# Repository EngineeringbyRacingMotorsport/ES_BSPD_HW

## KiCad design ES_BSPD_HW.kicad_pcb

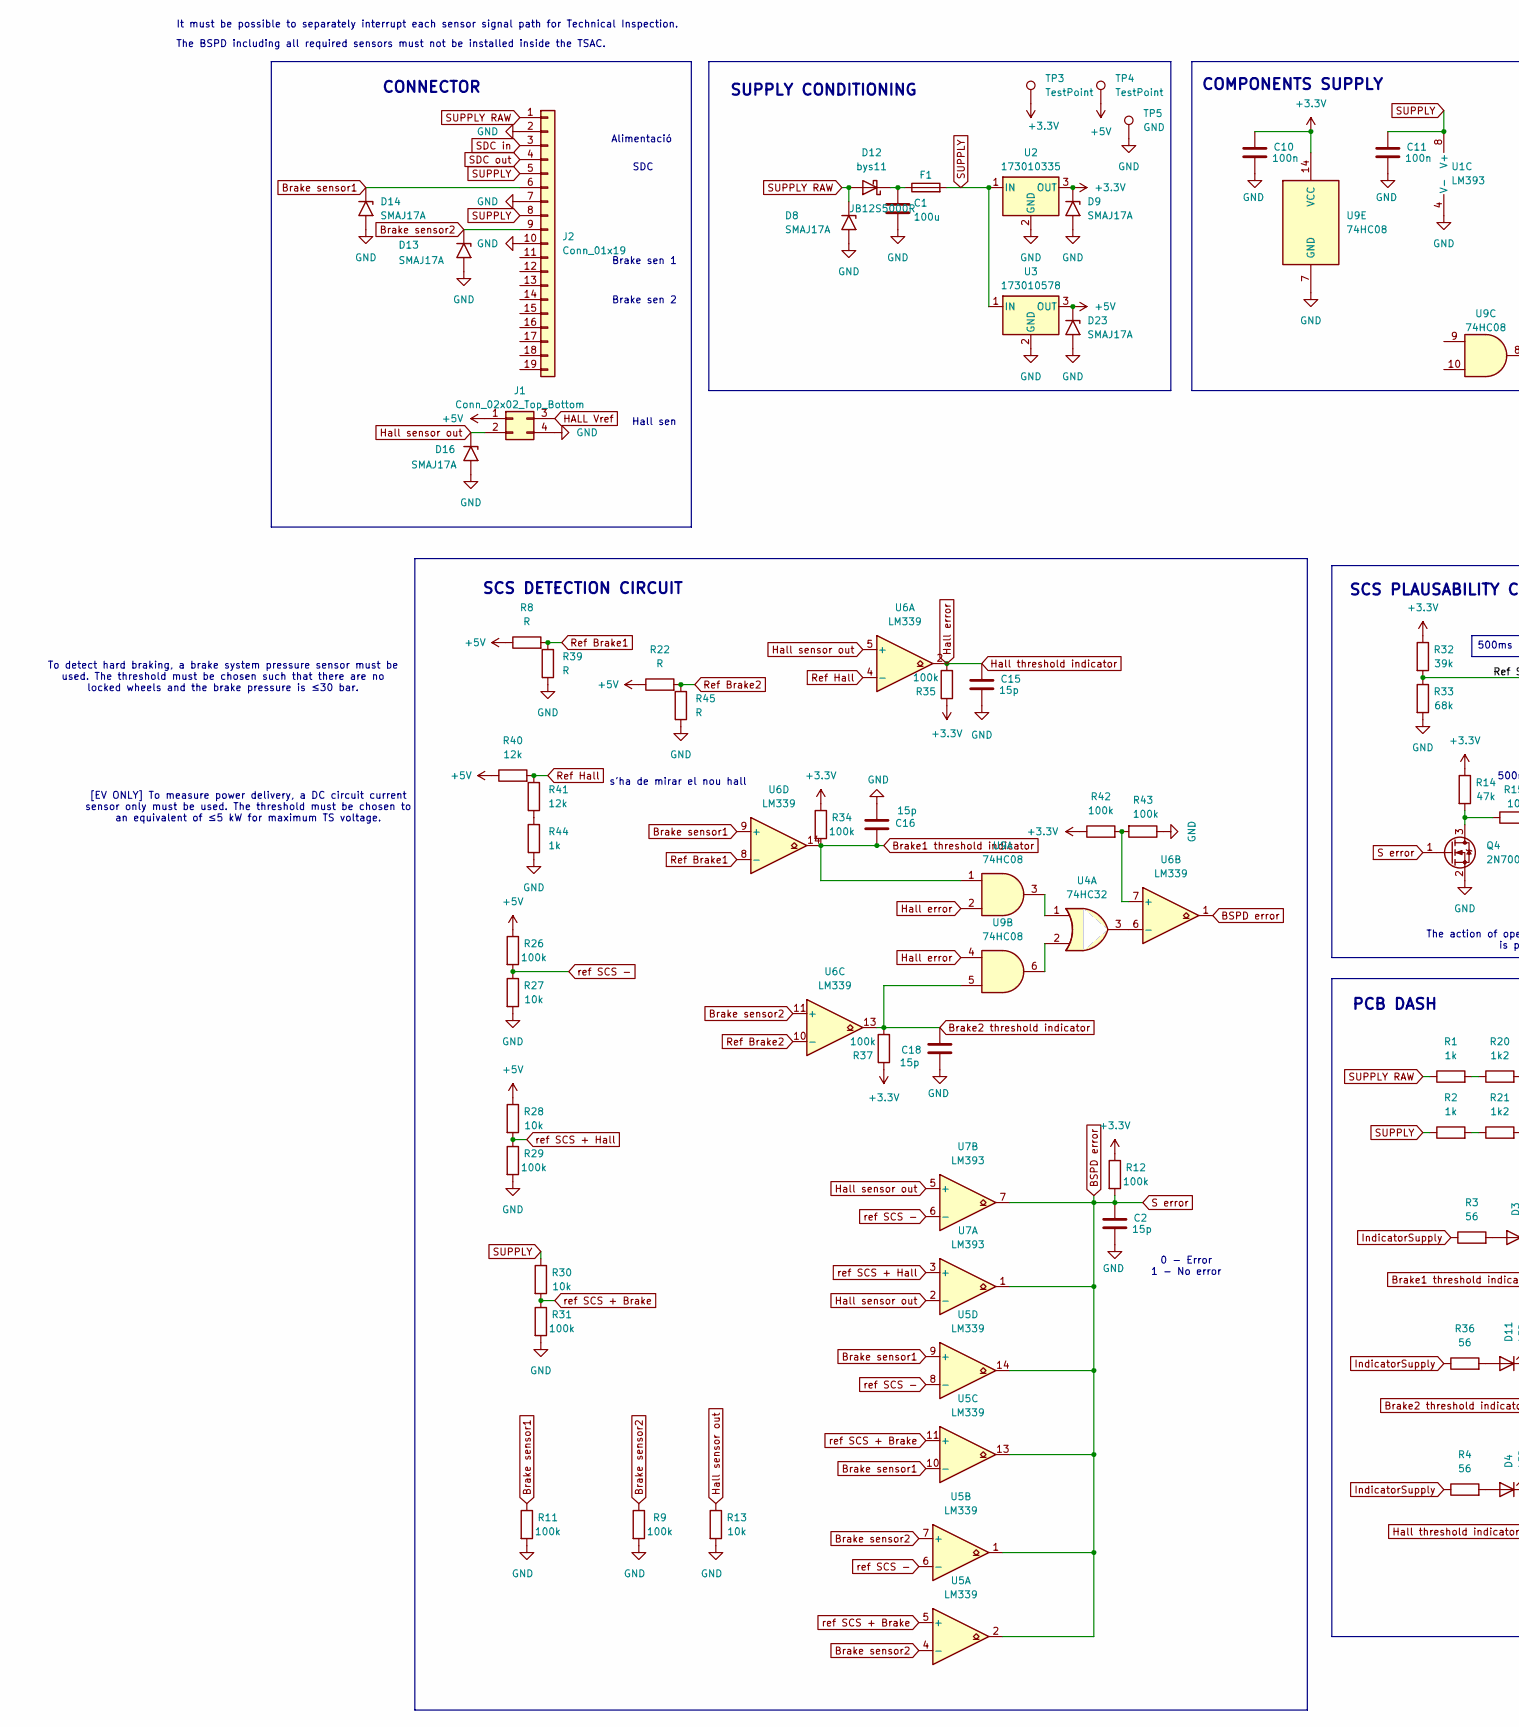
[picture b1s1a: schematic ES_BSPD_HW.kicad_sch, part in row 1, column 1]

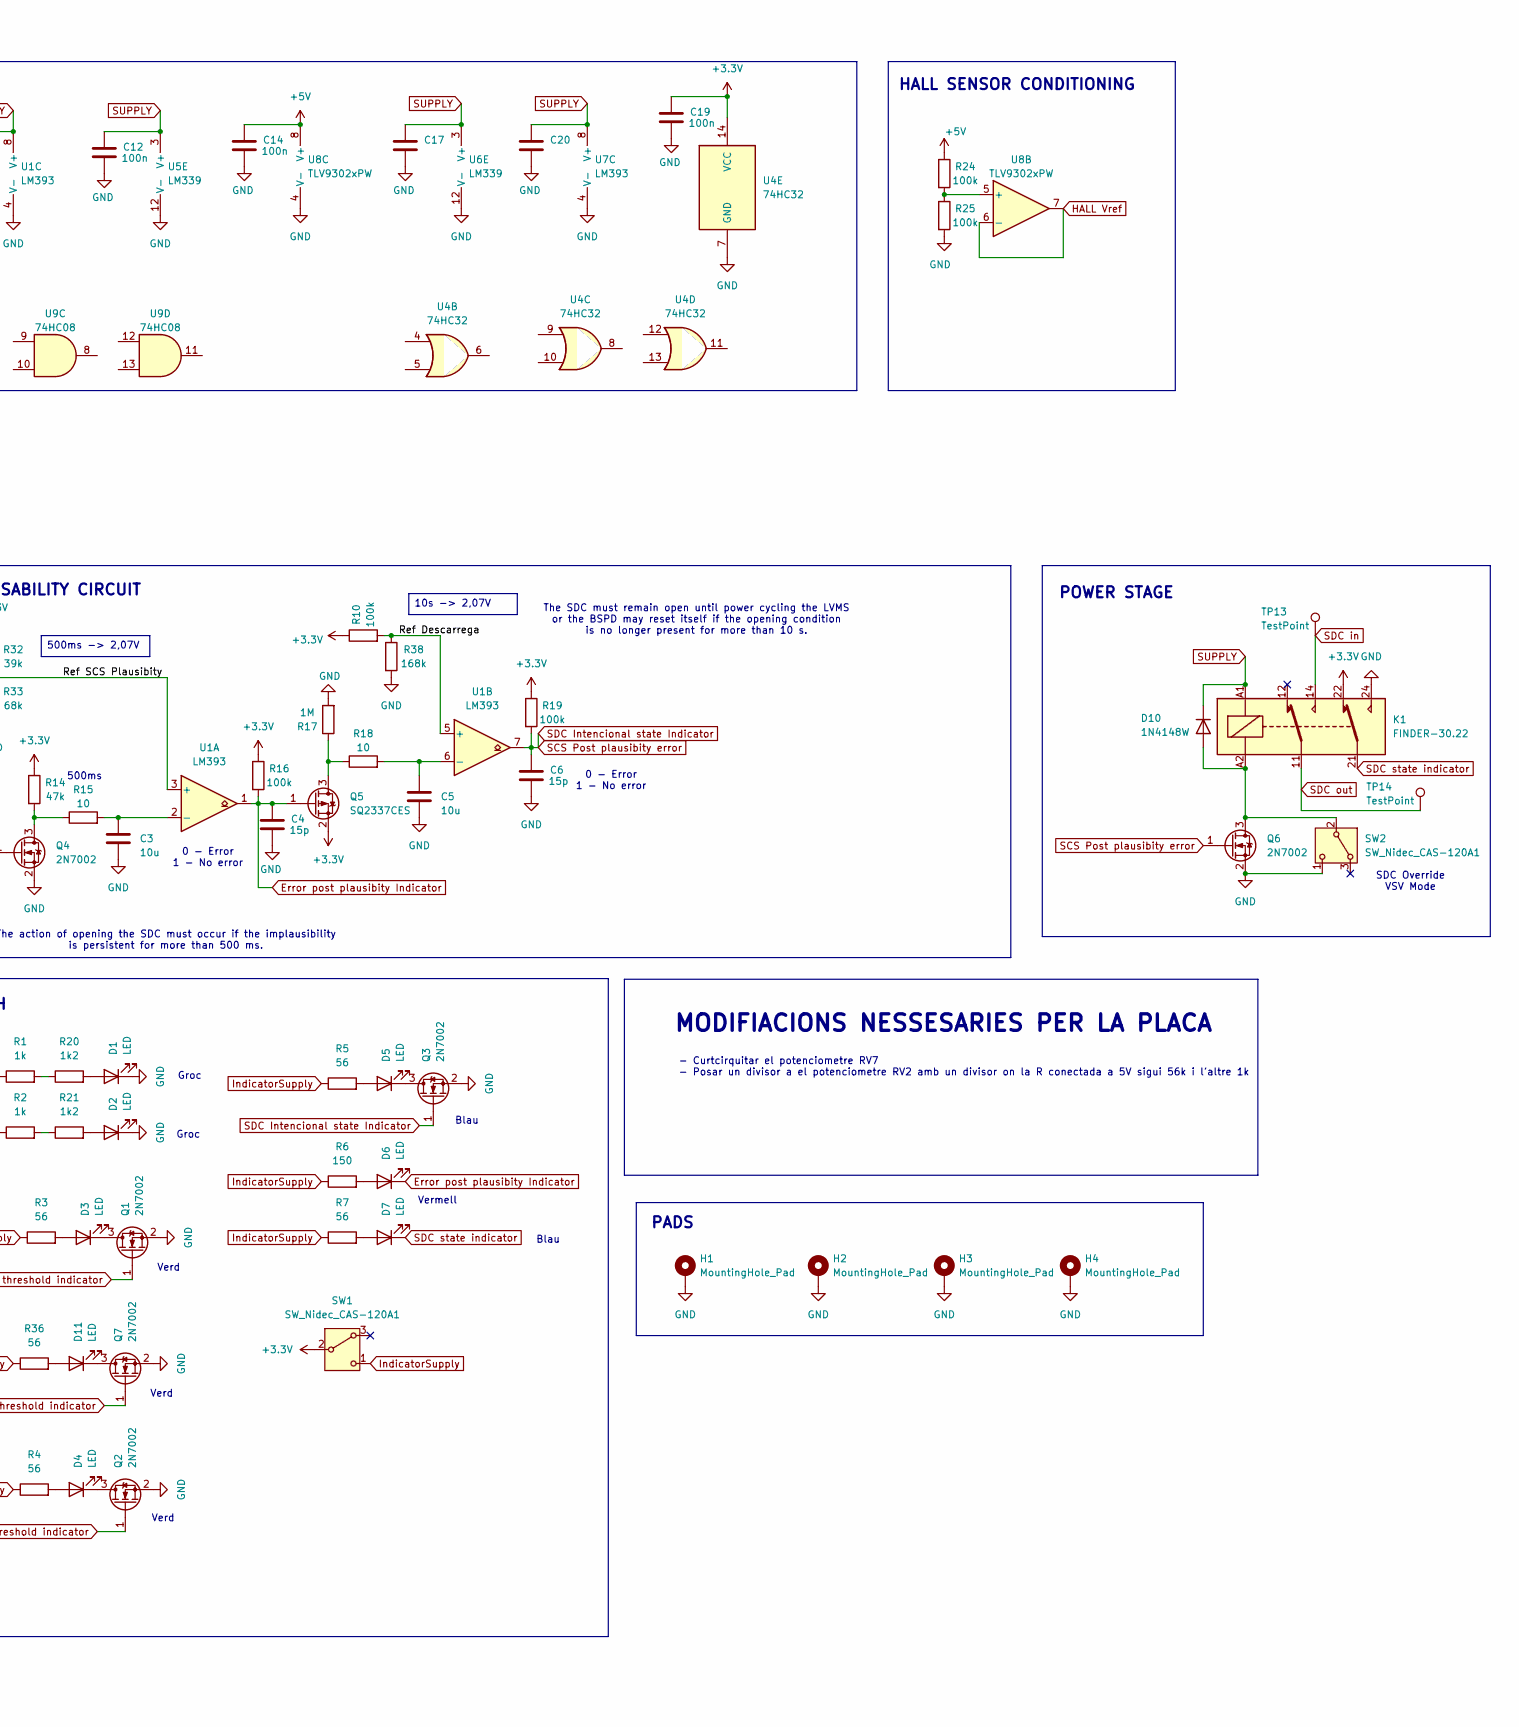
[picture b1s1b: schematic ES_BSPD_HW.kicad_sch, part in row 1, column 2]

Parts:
C1: 100u; CP_Elec_10x10
C2, C4, C6, C15, C16, C18: 15p; C_0603_1608Metric
C3, C5: 10u; C_0603_1608Metric
C10, C11, C12, C14, C17, C19, C20: 100n; C_0603_1608Metric
D1, D2, D3, D4, D5, D6, D7, D11: LED; LED_0603_1608Metric
D8, D9, D13, D14, D16, D23: SMAJ17A; D_SMB
D10: 1N4148W; D_SOD-123
D12: bys11; D_SMA
F1: JB12S5000R; Fuse_1206_3216Metric
H1, H2, H3, H4: MountingHole_Pad; MountingHole_3.5mm_Pad_Via
J1: Conn_02x02_Top_Bottom; Molex_Nano-Fit_105310-xx04_2x02_P2.50mm_Vertical
J2: Conn_01x19; CKB.M19.GLVG
K1: FINDER-30.22; Relay_DPDT_Finder_30.22
Q1, Q2, Q3, Q4, Q6, Q7: 2N7002; SOT-23
Q5: SQ2337CES; SOT-23
R1, R2: 1k; R_1206_3216Metric
R3, R4, R5, R7, R36: 56; R_0603_1608Metric
R6: 150; R_0603_1608Metric
R8, R22, R39, R45: R; R_0603_1608Metric
R9, R10, R11, R12, R16, R19, R24, R25, R26, R29, R31, R34, R35, R37, R42, R43: 100k; R_0603_1608Metric
R13, R27, R28, R30: 10k; R_0603_1608Metric
R14: 47k; R_0603_1608Metric
R15, R18: 10; R_0603_1608Metric
R17: 1M; R_0603_1608Metric
R20, R21: 1k2; R_1206_3216Metric
R32: 39k; R_0603_1608Metric
R33: 68k; R_0603_1608Metric
R38: 168k; R_0603_1608Metric
R40, R41: 12k; R_0603_1608Metric
R44: 1k; R_0603_1608Metric
SW1, SW2: SW_Nidec_CAS-120A1; Nidec_Copal_CAS-120A
TP3, TP4, TP13, TP14: TestPoint; TestPoint_Pad_D1.0mm
TP5: GND; TestPoint_Pad_D1.0mm
U1, U7: LM393; TSSOP-8_4.4x3mm_P0.65mm
U2: 173010335; Converter_DCDC_RECOM_R-78E-0.5_THT
U3: 173010578; Converter_DCDC_RECOM_R-78E-0.5_THT
U4: 74HC32; TSSOP-14_4.4x5mm_P0.65mm
U5, U6: LM339; TSSOP-14_4.4x5mm_P0.65mm
U8: TLV9302xPW; TSSOP-8_4.4x3mm_P0.65mm
U9: 74HC08; TSSOP-14_4.4x5mm_P0.65mm

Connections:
+3.3V: C10.1, C19.1, D9.1 (A1), K1.22, Q5.2 (S), R10.1, R12.1, R14.1, R16.1, R19.1, R32.1, R34.1, R35.1, R37.1, R42.1, SW1.2 (B), TP3.1, U2.3 (OUT), U4.14 (VCC), U9.14 (VCC)
+5V: C14.1, D23.1 (A1), J1.1, R8.1, R22.1, R24.1, R26.1, R28.1, R40.1, TP4.1, U3.3 (OUT), U8.8 (V+)
/Ref Descarrega: R10.2, R38.1, U1.5 (+)
/Ref SCS Plausibity: R32.2, R33.1, U1.3 (+)
BSPD error: C2.1, Q4.1 (G), R12.2, U5.1, U5.2, U5.13, U5.14, U6.1, U7.1, U7.7
Brake1 threshold indicator: C16.1, Q1.1 (G), R34.2, U6.14, U9.1
Brake2 threshold indicator: C18.1, Q7.1 (G), R37.2, U6.13, U9.5
Brake sensor1: D14.1 (A1), J2.6, R11.1, U5.9 (+), U5.10 (-), U6.9 (+)
Brake sensor2: D13.1 (A1), J2.9, R9.1, U5.4 (-), U5.7 (+), U6.11 (+)
Error post plausibity Indicator: C4.1, D6.1 (K), Q5.1 (G), R16.2, U1.1
GND: C1.2, C2.2, C3.2, C4.2, C5.2, C6.2, C10.2, C11.2, C12.2, C14.2, C15.2, C16.2, C17.2, C18.2, C19.2, C20.2, D1.1 (K), D2.1 (K), D8.2 (A2), D9.2 (A2), D13.2 (A2), D14.2 (A2), D16.2 (A2), D23.2 (A2), H1.1 (1_1), H2.1 (1_1), H3.1 (1_1), H4.1 (1_1), J1.4, J2.2, J2.7, J2.10, K1.24, Q1.2 (S), Q2.2 (S), Q3.2 (S), Q4.2 (S), Q6.2 (S), Q7.2 (S), R9.2, R11.2, R13.2, R17.2, R25.2, R27.2, R29.2, R31.2, R33.2, R38.2, R39.1, R43.1, R44.1, R45.1, SW2.1 (C), TP5.1, U1.4 (V-), U2.2 (GND), U3.2 (GND), U4.7 (GND), U5.12 (V-), U6.12 (V-), U7.4 (V-), U8.4 (V-), U9.7 (GND)
HALL Vref: J1.3, U8.6 (-), U8.7
Hall error: C15.1, Q2.1 (G), R35.2, U6.2, U9.2, U9.4
Hall sensor out: D16.1 (A1), J1.2, R13.1, U6.5 (+), U7.2 (-), U7.5 (+)
IndicatorSupply: R3.1, R4.1, R5.1, R6.1, R7.1, R36.1, SW1.1 (C)
unnamed: D1.2 (A), R20.2
unnamed: D2.2 (A), R21.2
unnamed: D3.2 (A), R3.2
unnamed: D3.1 (K), Q1.3 (D)
unnamed: D4.2 (A), R4.2
unnamed: D4.1 (K), Q2.3 (D)
unnamed: D5.2 (A), R5.2
unnamed: D5.1 (K), Q3.3 (D)
unnamed: D6.2 (A), R6.2
unnamed: D7.2 (A), R7.2
unnamed: D10.2 (A), K1.A2, Q6.3 (D), SW2.2 (B)
unnamed: D11.2 (A), R36.2
unnamed: D11.1 (K), Q7.3 (D)
unnamed: C1.1, D12.1 (K), F1.1
unnamed: Q4.3 (D), R14.2, R15.1
unnamed: Q5.3 (D), R17.1, R18.1
unnamed: R1.2, R20.1
unnamed: R2.2, R21.1
unnamed: R41.1, R44.2
unnamed: C3.1, R15.2, U1.2 (-)
unnamed: C5.1, R18.2, U1.6 (-)
unnamed: U4.1, U9.3
unnamed: U4.2, U9.6
unnamed: R42.2, R43.2, U6.7 (+)
unnamed: U4.3, U6.6 (-)
unnamed: R24.2, R25.1, U8.5 (+)
Ref Brake1: R8.2, R39.2, U6.8 (-)
Ref Brake2: R22.2, R45.2, U6.10 (-)
Ref Hall: R40.2, R41.2, U6.4 (-)
SCS Post plausibity error: C6.1, Q3.1 (G), Q6.1 (G), R19.2, U1.7
SDC in: J2.3, K1.14, TP13.1
SDC out: J2.4, K1.11, TP14.1
SDC state indicator: D7.1 (K), K1.21
SUPPLY: C11.1, C12.1, C17.1, C20.1, D10.1 (K), F1.2, J2.5, J2.8, K1.A1, R2.1, R30.1, U1.8 (V+), U2.1 (IN), U3.1 (IN), U5.3 (V+), U6.3 (V+), U7.8 (V+)
SUPPLY RAW: D8.1 (A1), D12.2 (A), J2.1, R1.1
ref SCS + Brake: R30.2, R31.1, U5.5 (+), U5.11 (+)
ref SCS + Hall: R28.2, R29.1, U7.3 (+)
ref SCS -: R26.2, R27.1, U5.6 (-), U5.8 (-), U7.6 (-)

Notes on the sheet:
SCS PLAUSABILITY CIRCUIT
SDC
Groc
[EV ONLY] To measure power delivery, a DC circuit current sensor only must be used. The threshold must be chosen to an equivalent of ≤5 kW for maximum TS voltage.
0 - Error 1 - No error
HALL SENSOR CONDITIONING
Blau
PADS
The action of opening the SDC must occur if the implausibility is persistent for more than 500 ms.
PCB DASH
Brake sen 1
The SDC must remain open until power cycling the LVMS or the BSPD may reset itself if the opening condition is no longer present for more than 10 s.
- Curtcirquitar el potenciometre RV7 - Posar un divisor a el potenciometre RV2 amb un divisor on la R conectada a 5V sigui 56k i l'altre 1k
s'ha de mirar el nou hall
Brake sen 2
COMPONENTS SUPPLY
Verd
Alimentació
Hall sen
SUPPLY CONDITIONING
It must be possible to separately interrupt each sensor signal path for Technical Inspection.
SCS DETECTION CIRCUIT
POWER STAGE
500ms
MODIFIACIONS NESSESARIES PER LA PLACA
To detect hard braking, a brake system pressure sensor must be used. The threshold must be chosen such that there are no locked wheels and the brake pressure is ≤30 bar.
Vermell
SDC Override VSV Mode
The BSPD including all required sensors must not be installed inside the TSAC.
CONNECTOR
500ms -> 2,07V
10s -> 2,07V

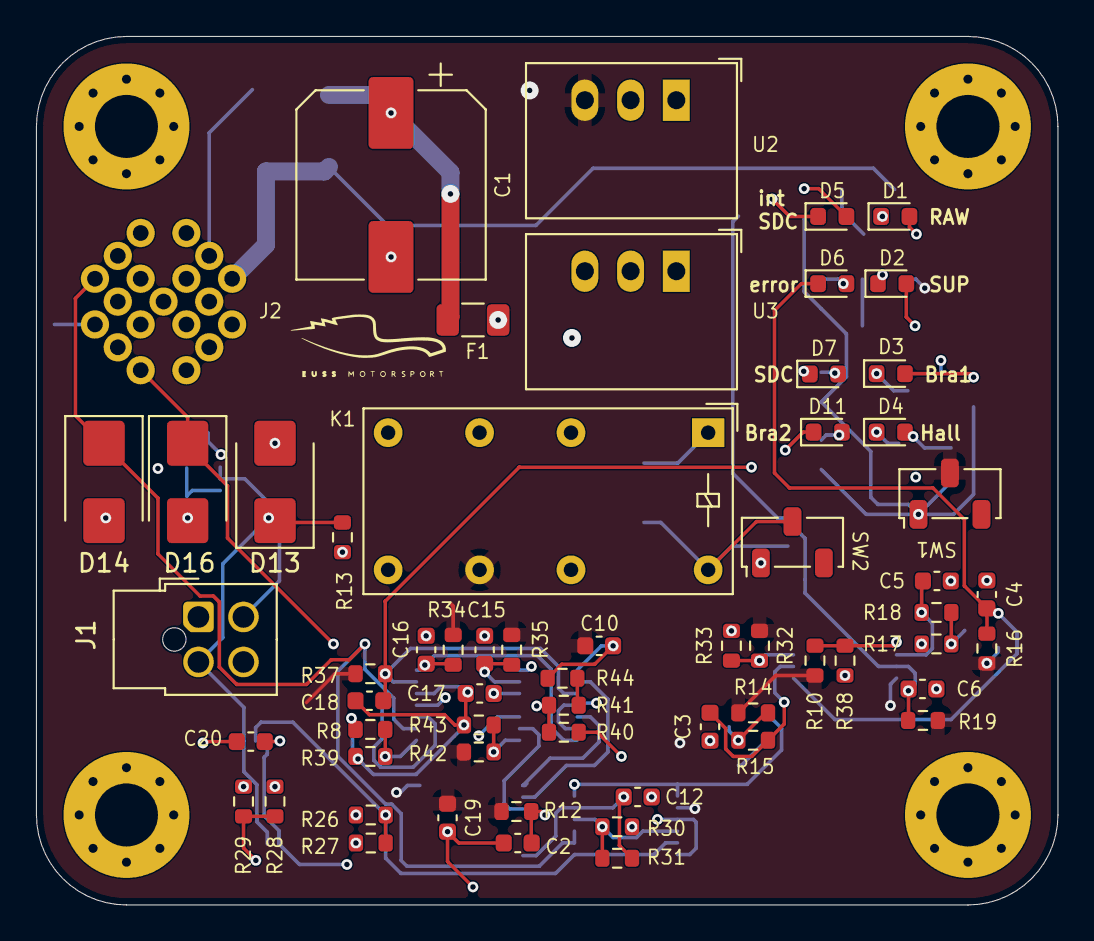
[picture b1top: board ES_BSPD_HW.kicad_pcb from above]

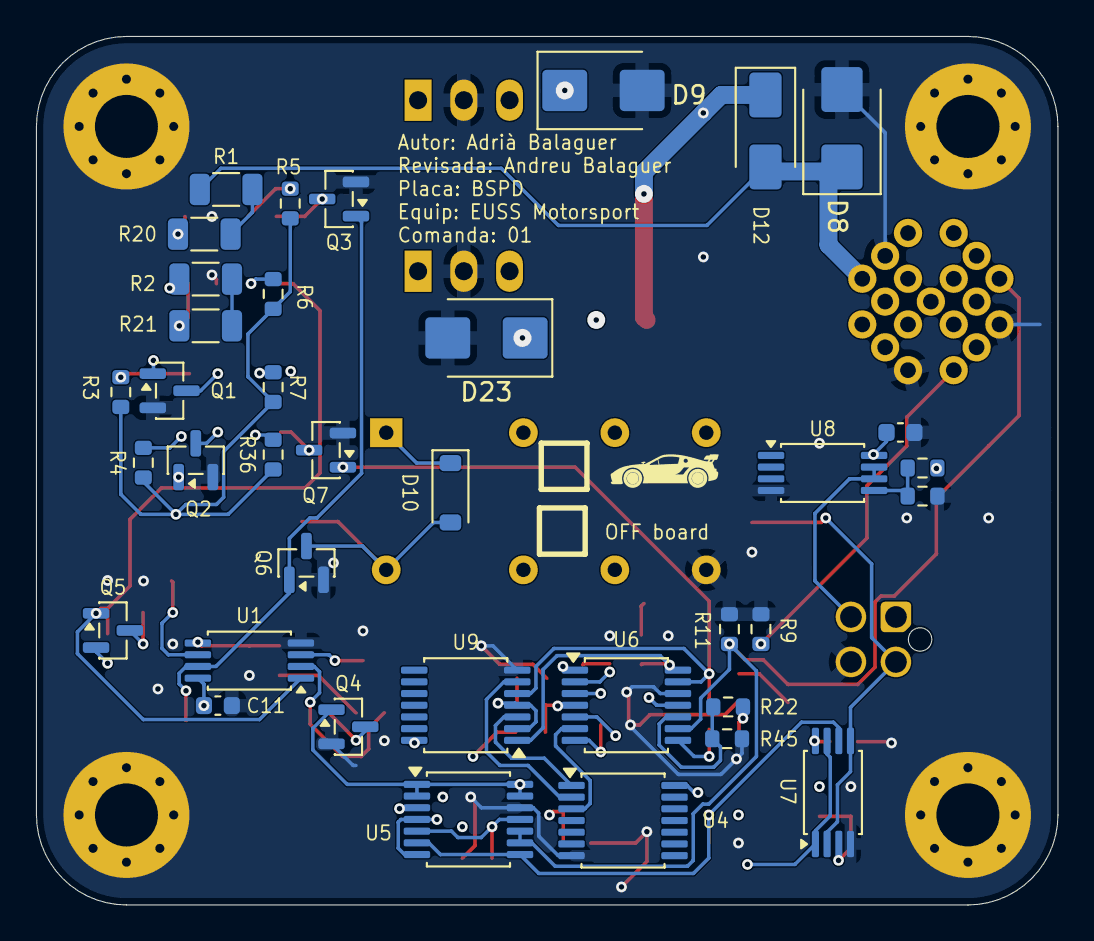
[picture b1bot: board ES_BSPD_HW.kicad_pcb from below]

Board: 4 copper layers, 56.8 x 48.2 mm, 102 parts (37 on the bottom side), 53 nets.

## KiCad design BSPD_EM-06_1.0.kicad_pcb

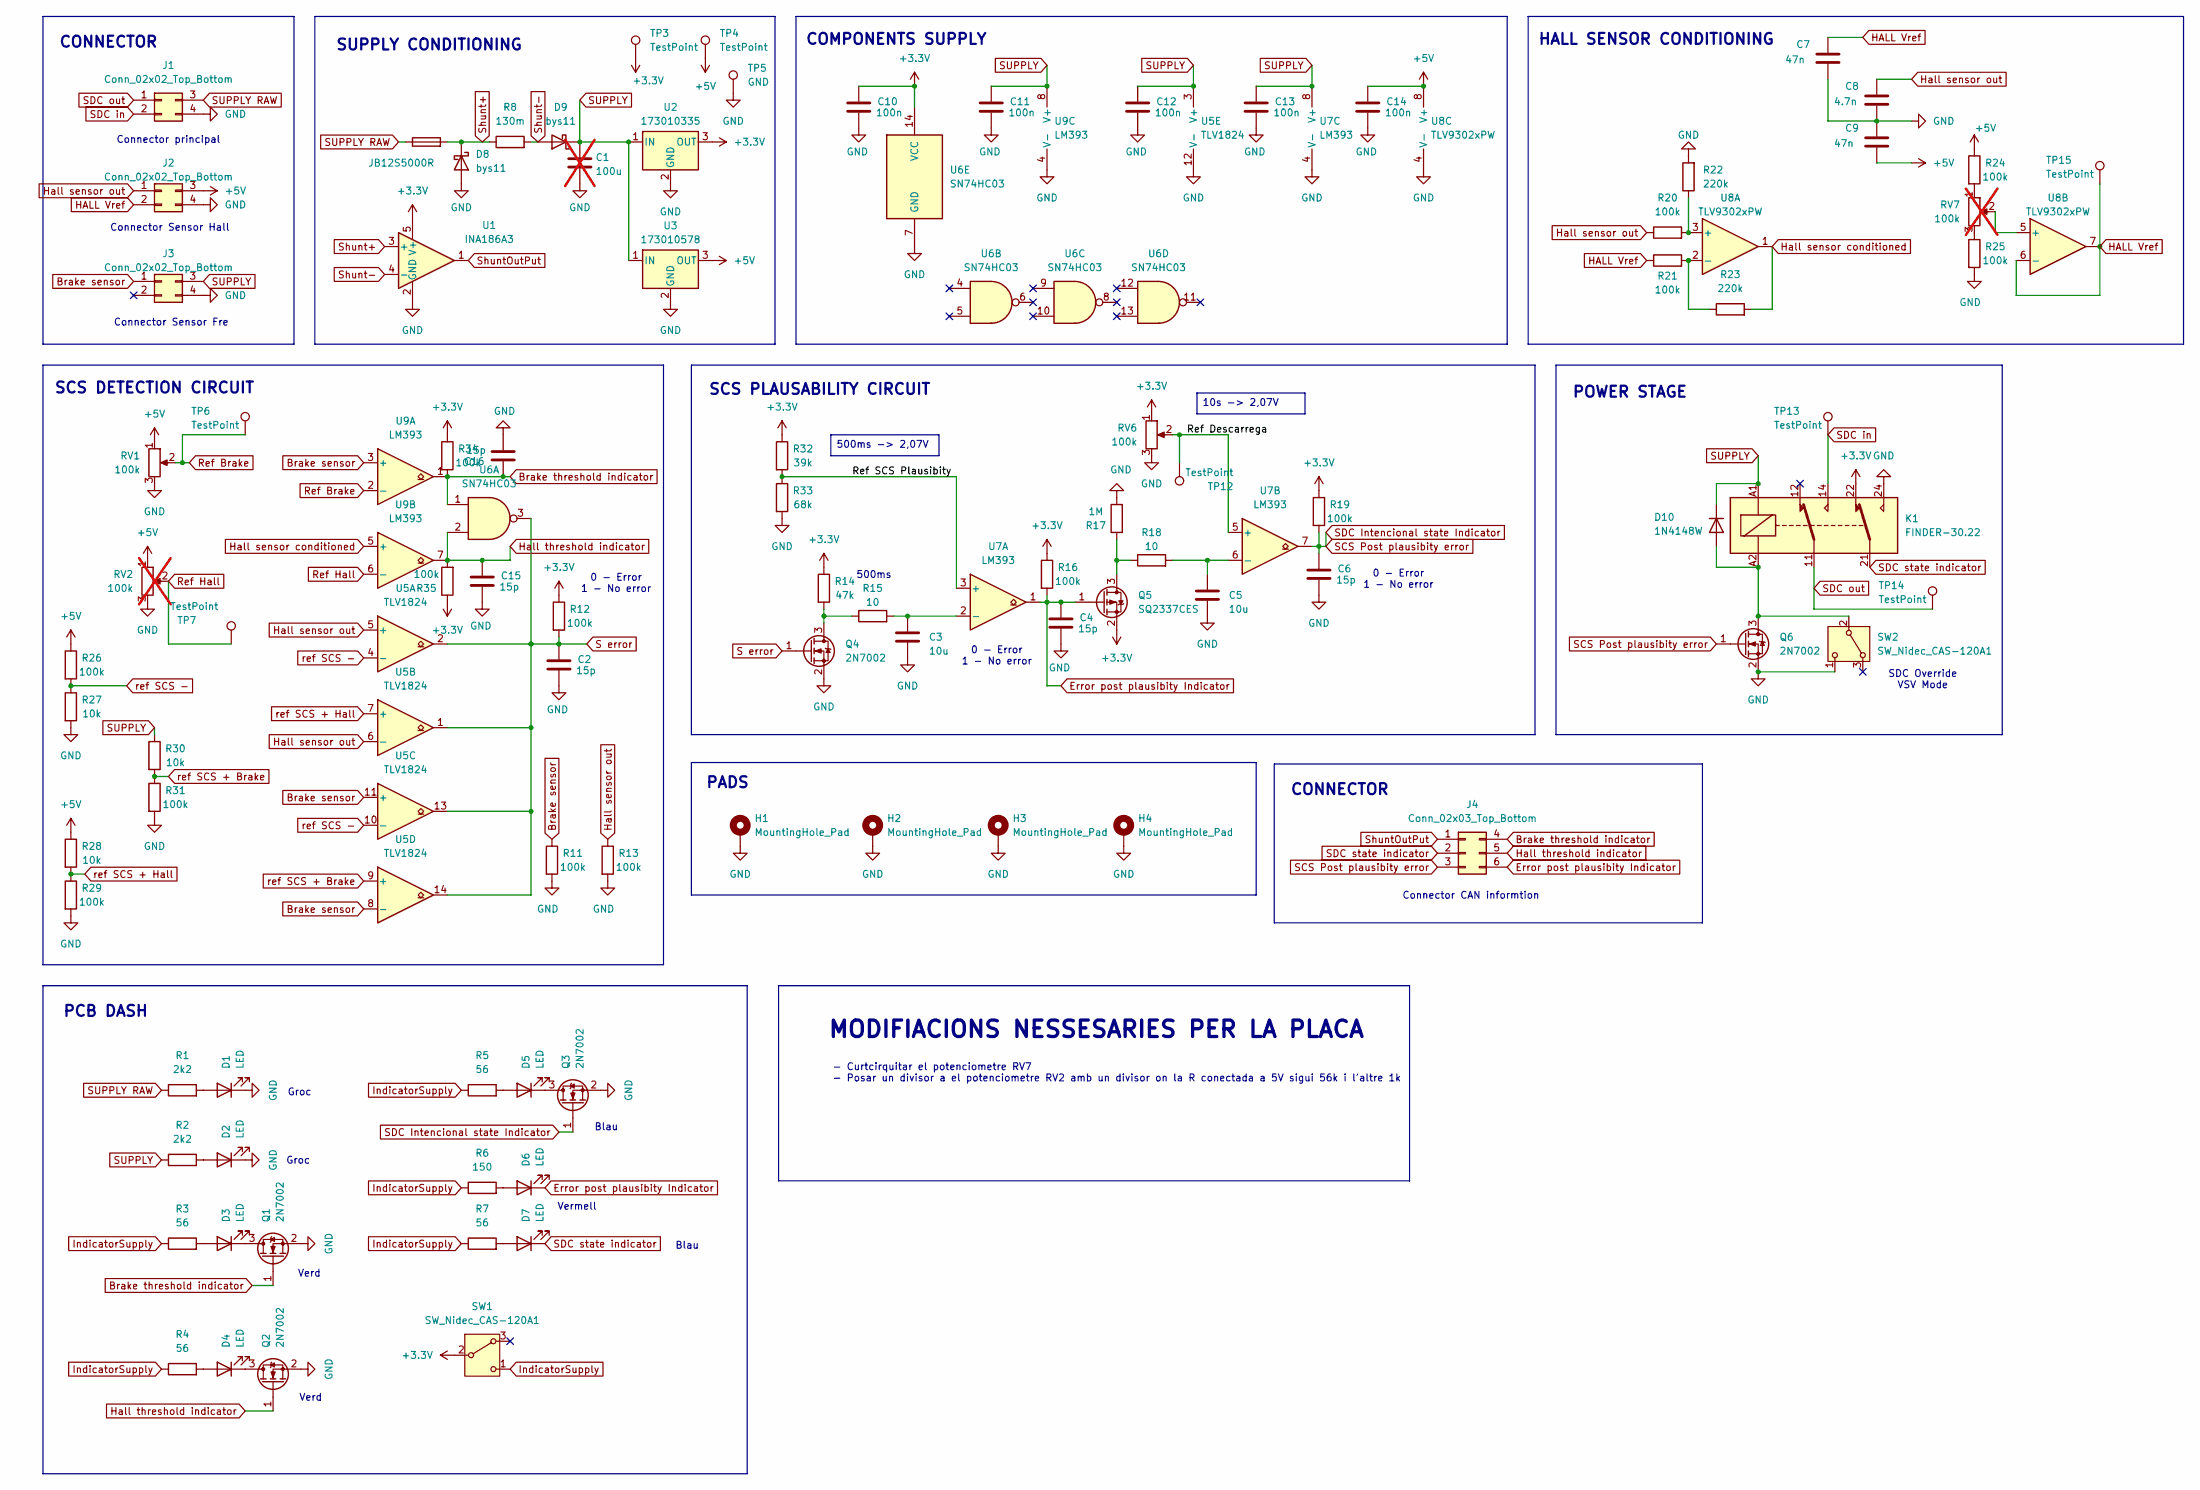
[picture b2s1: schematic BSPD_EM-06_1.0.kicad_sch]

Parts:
C1: 100u; CP_Elec_10x10; not fitted
C2, C4, C6, C15, C16: 15p; C_1206_3216Metric
C3, C5: 10u; C_1206_3216Metric
C7, C9: 47n; C_1206_3216Metric
C8: 4.7n; C_1206_3216Metric
C10, C11, C12, C13, C14: 100n; C_1206_3216Metric
D1, D2, D3, D4, D5, D6, D7: LED; LED_0603_1608Metric
D8, D9: bys11; D_SMA
D10: 1N4148W; D_SOD-123
F1: JB12S5000R; Fuse_1206_3216Metric
H1, H2, H3, H4: MountingHole_Pad; MountingHole_3.5mm_Pad_Via
J1: Conn_02x02_Top_Bottom; j4
J2, J3: Conn_02x02_Top_Bottom; Molex_Nano-Fit_105314-xx04_2x02_P2.50mm_Horizontal
J4: Conn_02x03_Top_Bottom; rv7
K1: FINDER-30.22; Relay_DPDT_Finder_30.22
Q1, Q2, Q3, Q4, Q6: 2N7002; SOT-23
Q5: SQ2337CES; SOT-23
R1, R2: 2k2; R_1206_3216Metric
R3, R4, R5, R7: 56; R_1206_3216Metric
R6: 150; R_1206_3216Metric
R8: 130m; R_1206_3216Metric
R11, R12, R13, R16, R19, R20, R21, R24, R25, R26, R29, R31, R34, R35: 100k; R_1206_3216Metric
R14: 47k; R_1206_3216Metric
R15, R18: 10; R_1206_3216Metric
R17: 1M; R_1206_3216Metric
R22, R23: 220k; R_1206_3216Metric
R27, R28, R30: 10k; R_1206_3216Metric
R32: 39k; R_1206_3216Metric
R33: 68k; R_1206_3216Metric
RV1, RV6: 100k; Potentiometer_Vishay_T93YA_Vertical
RV2, RV7: 100k; Potentiometer_Vishay_T93YA_Vertical; not fitted
SW1, SW2: SW_Nidec_CAS-120A1; Nidec_Copal_CAS-120A
TP3, TP4, TP6, TP7, TP12, TP13, TP14, TP15: TestPoint; TestPoint_Pad_D1.0mm
TP5: GND; TestPoint_Pad_D1.0mm
U1: INA186A3; SOT-23-5
U2: 173010335; Converter_DCDC_RECOM_R-78E-0.5_THT
U3: 173010578; Converter_DCDC_RECOM_R-78E-0.5_THT
U5: TLV1824; TSSOP-14_4.4x5mm_P0.65mm
U6: SN74HC03; TSSOP-14_4.4x5mm_P0.65mm
U7, U9: LM393; TSSOP-8_4.4x3mm_P0.65mm
U8: TLV9302xPW; TSSOP-8_4.4x3mm_P0.65mm

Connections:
+3.3V: C10.1, K1.22, Q5.2 (S), R12.1, R14.1, R16.1, R19.1, R32.1, R34.1, R35.1, RV6.1, SW1.2 (B), TP3.1, U1.5 (V+), U2.3 (OUT), U6.14 (VCC)
+5V: C9.1, C14.1, J2.3, R24.1, R26.1, R28.1, RV1.1, RV2.1, TP4.1, U3.3 (OUT), U8.8 (V+)
/Ref Descarrega: RV6.2, TP12.1, U7.5 (+)
/Ref SCS Plausibity: R32.2, R33.1, U7.3 (+)
Brake sensor: J3.1, R11.1, U5.8 (-), U5.11 (+), U9.3 (+)
Brake threshold indicator: C16.1, J4.4, Q1.1 (G), R34.2, U6.1, U9.1
Error post plausibity Indicator: C4.1, D6.1 (K), J4.6, Q5.1 (G), R16.2, U7.1
GND: C1.2, C2.2, C3.2, C4.2, C5.2, C6.2, C7.1, C8.1, C9.2, C10.2, C11.2, C12.2, C13.2, C14.2, C15.2, C16.2, D1.1 (K), D2.1 (K), D8.2 (A), H1.1, H2.1, H3.1, H4.1, J1.4, J2.4, J3.4, K1.24, Q1.2 (S), Q2.2 (S), Q3.2 (S), Q4.2 (S), Q6.2 (S), R11.2, R13.2, R17.2, R22.2, R25.2, R27.2, R29.2, R31.2, R33.2, RV1.3, RV2.3, RV6.3, SW2.1 (C), TP5.1, U1.2 (GND), U2.2 (GND), U3.2 (GND), U5.12 (V-), U6.7 (GND), U7.4 (V-), U8.4 (V-), U9.4 (V-)
HALL Vref: C7.2, J2.2, R21.1, TP15.1, U8.6 (-), U8.7
Hall sensor conditioned: R23.2, U8.1, U9.5 (+)
Hall sensor out: C8.2, J2.1, R13.1, R20.1, U5.5 (+), U5.6 (-)
Hall threshold indicator: C15.1, J4.5, Q2.1 (G), R35.2, U6.2, U9.7
IndicatorSupply: R3.1, R4.1, R5.1, R6.1, R7.1, SW1.1 (C)
unnamed: D1.2 (A), R1.2
unnamed: D2.2 (A), R2.2
unnamed: D3.2 (A), R3.2
unnamed: D3.1 (K), Q1.3 (D)
unnamed: D4.2 (A), R4.2
unnamed: D4.1 (K), Q2.3 (D)
unnamed: D5.2 (A), R5.2
unnamed: D5.1 (K), Q3.3 (D)
unnamed: D6.2 (A), R6.2
unnamed: D7.2 (A), R7.2
unnamed: D10.2 (A), K1.A2, Q6.3 (D), SW2.2 (B)
unnamed: Q4.3 (D), R14.2, R15.1
unnamed: Q5.3 (D), R17.1, R18.1
unnamed: R24.2, RV7.1
unnamed: R25.1, RV7.3
unnamed: C3.1, R15.2, U7.2 (-)
unnamed: C5.1, R18.2, U7.6 (-)
unnamed: R20.2, R22.1, U8.3 (+)
unnamed: R21.2, R23.1, U8.2 (-)
unnamed: RV7.2, U8.5 (+)
Ref Brake: RV1.2, TP6.1, U9.2 (-)
Ref Hall: RV2.2, TP7.1, U9.6 (-)
S error: C2.1, Q4.1 (G), R12.2, U5.1, U5.2, U5.13, U5.14, U6.3
SCS Post plausibity error: C6.1, J4.3, Q3.1 (G), Q6.1 (G), R19.2, U7.7
SDC in: J1.2, K1.14, TP13.1
SDC out: J1.1, K1.11, TP14.1
SDC state indicator: D7.1 (K), J4.2, K1.21
SUPPLY: C1.1, C11.1, C12.1, C13.1, D9.1 (K), D10.1 (K), J3.3, K1.A1, R2.1, R30.1, U2.1 (IN), U3.1 (IN), U5.3 (V+), U7.8 (V+), U9.8 (V+)
SUPPLY RAW: F1.1, J1.3, R1.1
Shunt+: D8.1 (K), F1.2, R8.1, U1.3 (+)
Shunt-: D9.2 (A), R8.2, U1.4 (-)
ShuntOutPut: J4.1, U1.1
ref SCS + Brake: R30.2, R31.1, U5.9 (+)
ref SCS + Hall: R28.2, R29.1, U5.7 (+)
ref SCS -: R26.2, R27.1, U5.4 (-), U5.10 (-)

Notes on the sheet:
SCS DETECTION CIRCUIT
Connector principal
HALL SENSOR CONDITIONING
CONNECTOR
Blau
COMPONENTS SUPPLY
MODIFIACIONS NESSESARIES PER LA PLACA
500ms
Verd
SUPPLY CONDITIONING
Connector CAN informtion
Groc
Connector Sensor Fre
PCB DASH
SDC Override VSV Mode
Vermell
SCS PLAUSABILITY CIRCUIT
0 - Error 1 - No error
- Curtcirquitar el potenciometre RV7 - Posar un divisor a el potenciometre RV2 amb un divisor on la R conectada a 5V sigui 56k i l'altre 1k
POWER STAGE
Connector Sensor Hall
PADS
500ms -> 2,07V
10s -> 2,07V

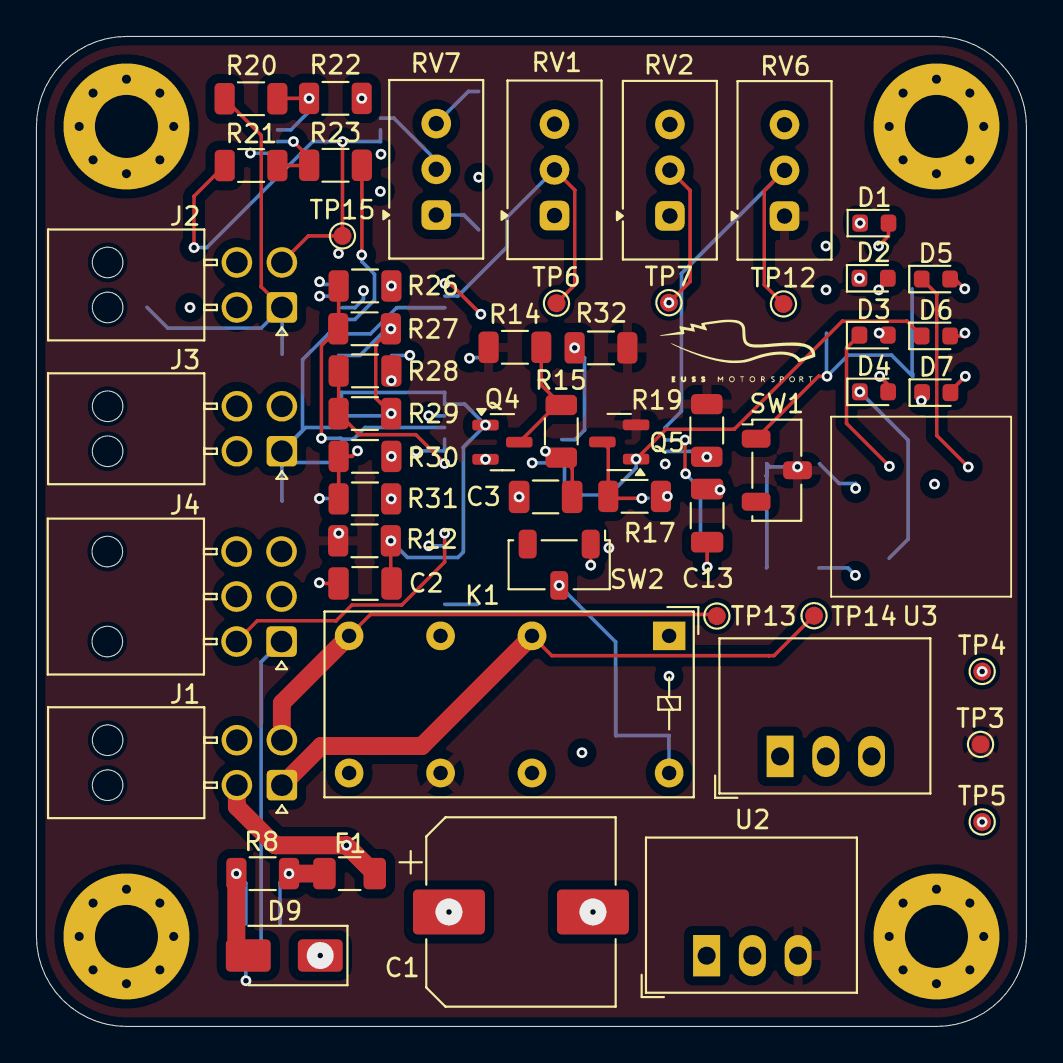
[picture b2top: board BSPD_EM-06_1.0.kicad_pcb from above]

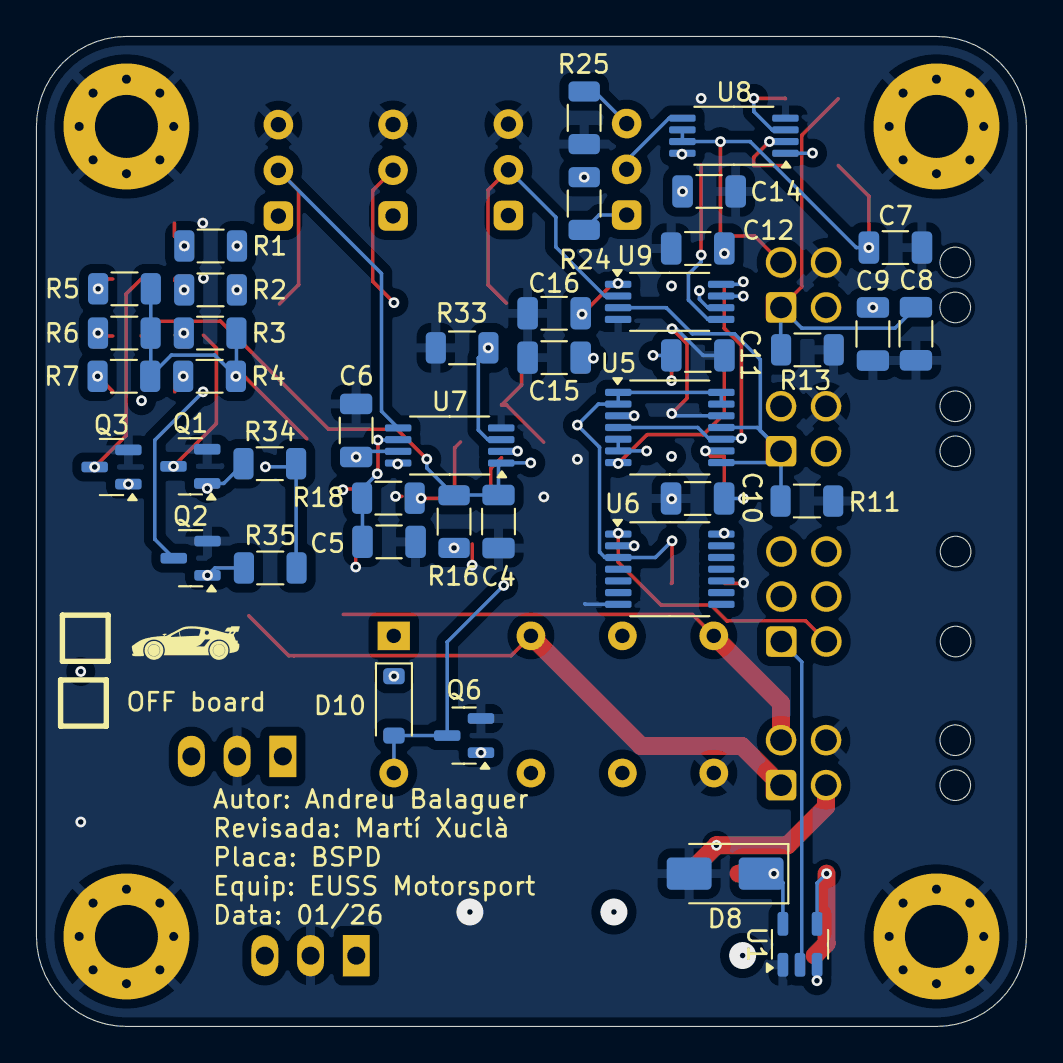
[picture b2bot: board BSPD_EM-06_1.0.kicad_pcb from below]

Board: 4 copper layers, 55.0 x 55.0 mm, 98 parts (40 on the bottom side), 48 nets.
